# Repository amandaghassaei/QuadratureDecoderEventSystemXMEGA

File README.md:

# QuadratureDecoderEventSystemXMEGA
code and schematics for implementing a qdec using the XMEGA's event system (not its built in qdec) for support of 4 qdecs on one xmega board

More info coming soon

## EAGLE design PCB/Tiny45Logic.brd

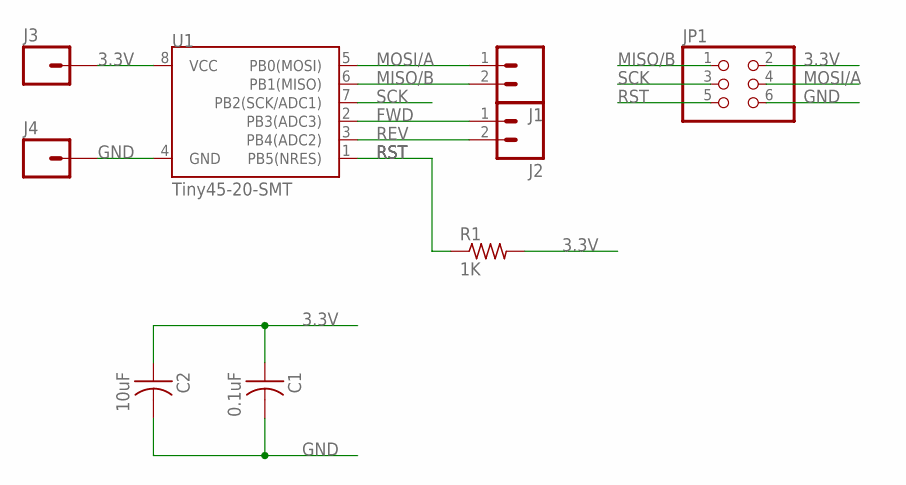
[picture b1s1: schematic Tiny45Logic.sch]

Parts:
C1: 0.1uF; C1206FAB
C2: 10uF; C1206FAB
J1, J2: M02PTH; 1X02
J3, J4: M01PTH; 1X01
JP1: PINHD-2X3-SMD; 2X03SMD
R1: 1K; R1206
U1: Tiny45-20-SMT; SO08-EIAJ

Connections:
3.3V: C1.1, C2.1, J3.1, JP1.2, R1.2, U1.8 (VCC)
FWD: J2.1, U1.2 (PB3(ADC3))
GND: C1.2, C2.2, J4.1, JP1.6, U1.4 (GND)
MISO/B: J1.2, JP1.1, U1.6 (PB1(MISO))
MOSI/A: J1.1, JP1.4, U1.5 (PB0(MOSI))
REV: J2.2, U1.3 (PB4(ADC2))
RST: JP1.5, R1.1, U1.1 (PB5(NRES))
SCK: JP1.3, U1.7 (PB2(SCK/ADC1))

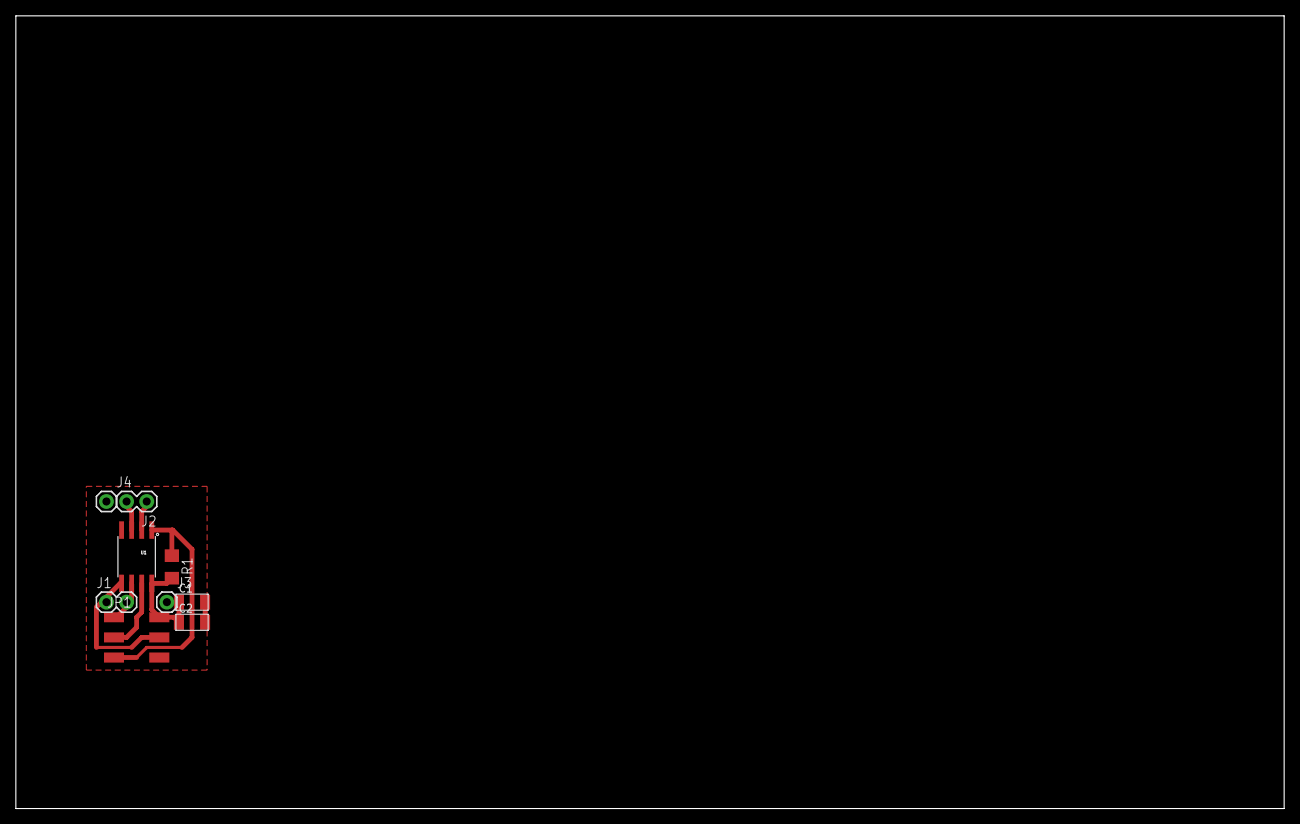
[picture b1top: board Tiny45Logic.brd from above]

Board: 2 copper layers, 160.0 x 100.0 mm, 9 parts (0 on the bottom side), 8 nets.

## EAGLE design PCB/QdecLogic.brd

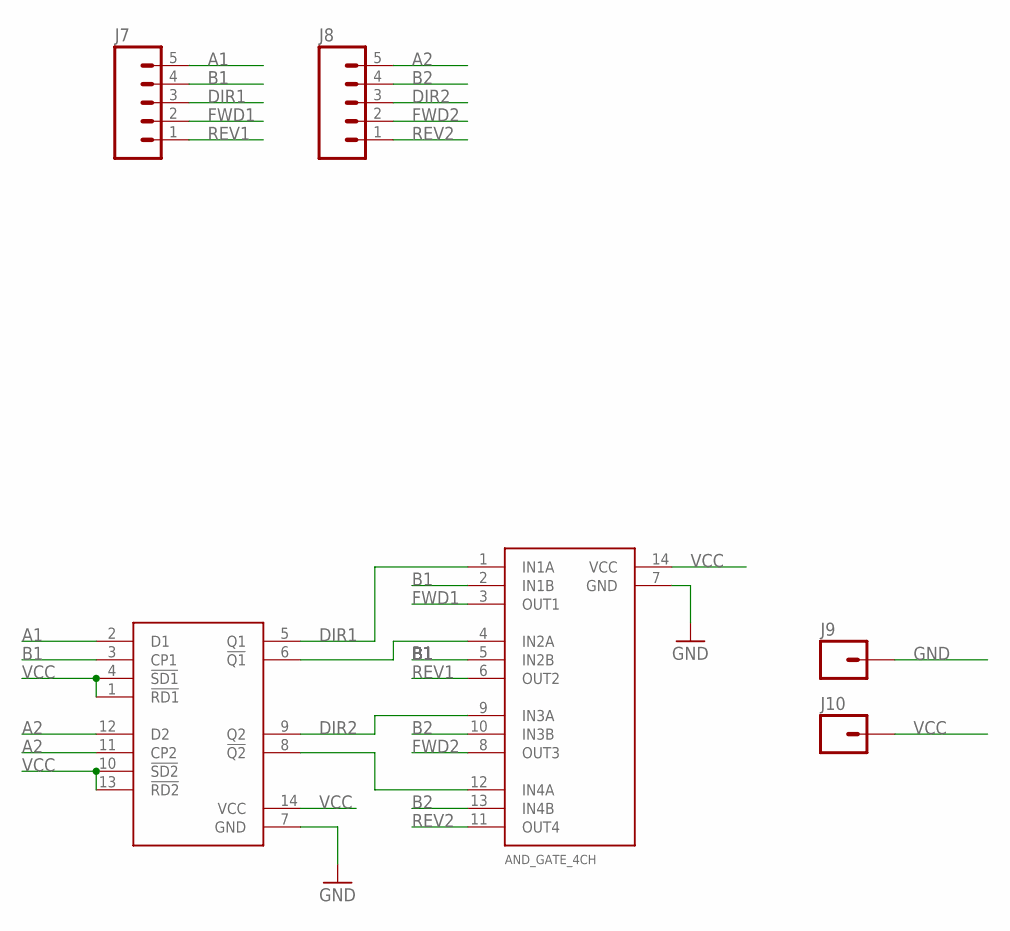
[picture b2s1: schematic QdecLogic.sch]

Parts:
J7, J8: M05NO_SILK; 1X05_NO_SILK
J9, J10: M01PTH_NO_SILK_YES_STOP; 1X01_NO_SILK
U$1: AND_GATE_4CH; 14-SOIC
U$2: FLIPFLOP_D-TYPE_2CH; 14-SOIC

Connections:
A1: J7.5, U$2.2 (D1)
A2: J8.5, U$2.12 (D2)
B1: J7.4, U$1.2 (IN1B), U$1.5 (IN2B), U$2.3 (CP1)
B2: J8.4, U$1.10 (IN3B), U$1.13 (IN4B), U$2.11 (CP2)
DIR1: J7.3, U$1.1 (IN1A), U$2.5 (Q1)
DIR2: J8.3, U$1.9 (IN3A), U$2.9 (Q2)
FWD1: J7.2, U$1.3 (OUT1)
FWD2: J8.2, U$1.8 (OUT3)
GND: J9.1, U$1.7 (GND), U$2.7 (GND)
unnamed: U$1.4 (IN2A), U$2.6 (!Q1)
unnamed: U$1.12 (IN4A), U$2.8 (!Q2)
REV1: J7.1, U$1.6 (OUT2)
REV2: J8.1, U$1.11 (OUT4)
VCC: J10.1, U$1.14 (VCC), U$2.1 (!RD1), U$2.4 (!SD1), U$2.10 (!SD2), U$2.13 (!RD2), U$2.14 (VCC)

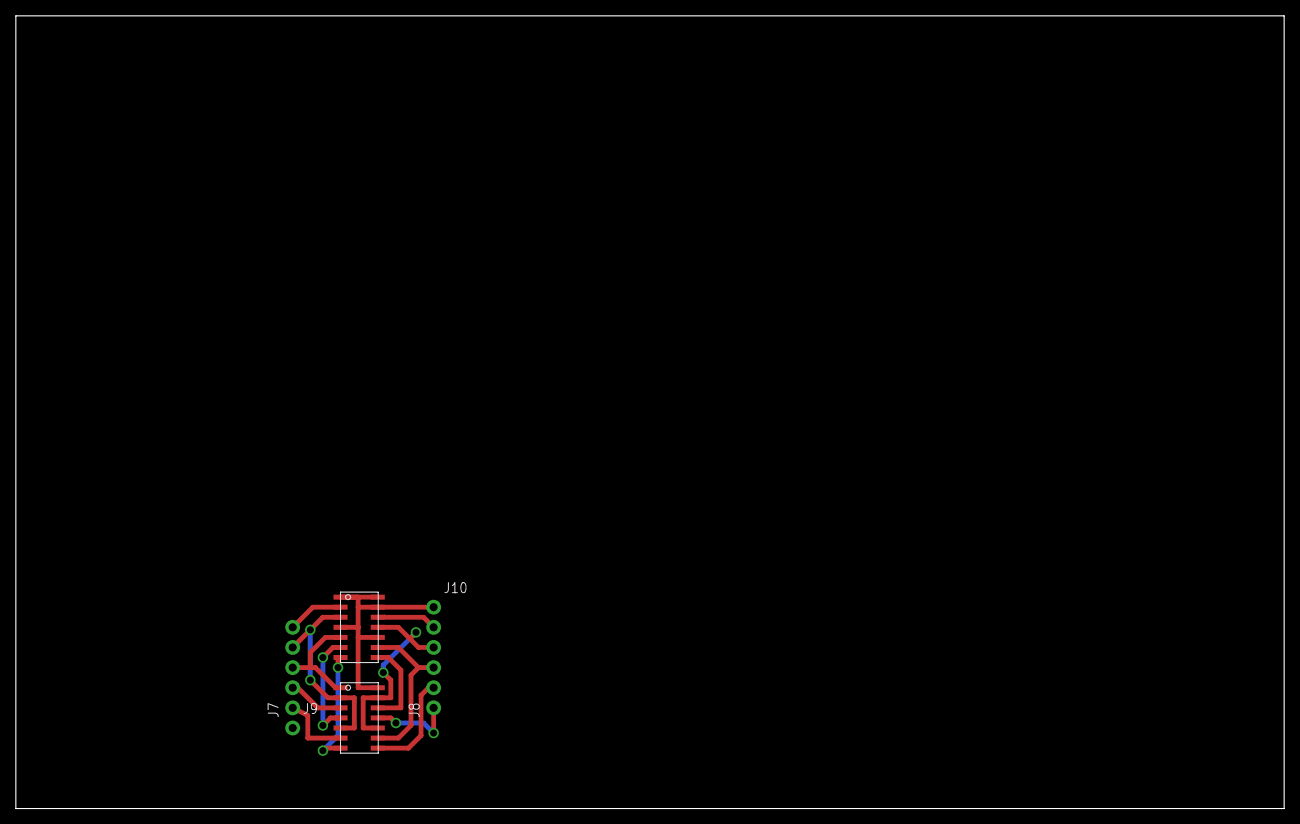
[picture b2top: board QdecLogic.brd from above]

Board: 2 copper layers, 160.0 x 100.0 mm, 6 parts (0 on the bottom side), 14 nets.

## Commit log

2016-06-26 first ocmmit
2016-06-26 schematic layout
2016-06-26 pngs
2016-06-26 small changes
2016-06-27 arrayed
2016-06-28 fixed pcb
2016-06-28 fixed pcb layout
2016-06-28 updated psd
2017-02-09 attiny45
2017-02-18 caps
2017-03-12 fixed dpi

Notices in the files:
parts and their libraries:
SparkFun-Connectors: Licensing: Creative Commons ShareAlike 4.0 International - https://creativecommons.org/licenses/by-sa/4.0
